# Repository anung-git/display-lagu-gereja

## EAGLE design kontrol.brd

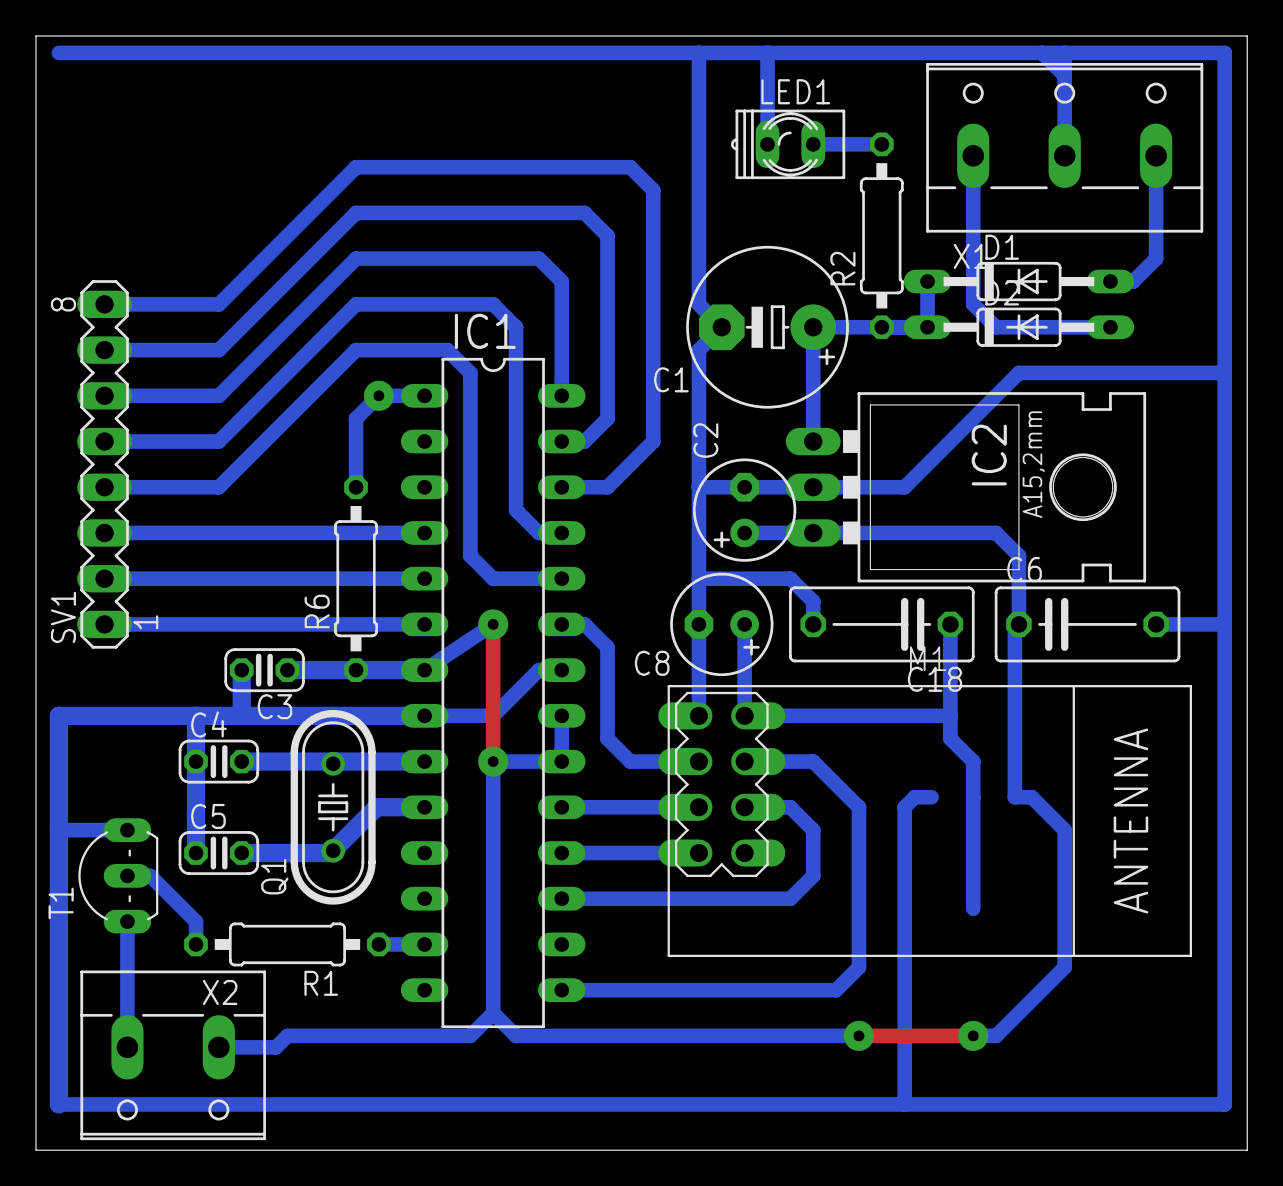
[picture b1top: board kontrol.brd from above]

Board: 2 copper layers, 67.3 x 61.9 mm, 23 parts (1 on the bottom side), 26 nets.

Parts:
C1: E5-8,5
C2, C8: E2,5-6
C3: 100n; C025-024X044
C4, C5: 22p; C025-024X044
C6, C18: C075-042X103
D1, D2: 1N4446; DO35-10
IC1: ATMega88*; DIL28-3
IC2: 78XXL
IC4: MC33269ST-5.0T3; SOT223
LED1: Q62902-B152
M1: WIRELESS-NRF24L01
Q1: 12MHz; HC49/S
R1, R2, R6: 10k; 0207/10
SV1: MA08-1
T1: TO92-CBE
X1: W237-3E
X2: W237-132

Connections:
+5V: C2.+, C3.1, C6.1, IC1.7, IC1.20, IC1.21, IC2.OUT, IC4.3, R6.1, X2.1
+5V1: C8.+, C18.1, IC4.2, IC4.4, M1.2
GND: C1.-, C2.-, C3.2, C4.1, C5.1, C6.2, C8.-, C18.2, IC1.8, IC1.22, IC2.GND, IC4.1, LED1.K, M1.1, T1.E, X1.2
unnamed: IC1.1, R6.2
unnamed: IC1.6, SV1.1
unnamed: IC1.5, SV1.2
unnamed: IC1.4, SV1.3
unnamed: IC1.24, SV1.4
unnamed: IC1.17, M1.6
unnamed: IC1.25, SV1.5
unnamed: IC1.26, SV1.8
unnamed: IC1.18, M1.7
unnamed: IC1.19, M1.5
unnamed: IC1.23, M1.3
unnamed: IC1.15, M1.4
unnamed: IC1.27, SV1.7
unnamed: IC1.28, SV1.6
unnamed: C1.+, D1.C, D2.C, IC2.IN, R2.1
unnamed: D2.A, X1.1
unnamed: D1.A, X1.3
unnamed: T1.C, X2.2
unnamed: IC1.13, R1.1
unnamed: R1.2, T1.B
unnamed: LED1.A, R2.2
unnamed: C4.2, IC1.9, Q1.2
unnamed: C5.2, IC1.10, Q1.1

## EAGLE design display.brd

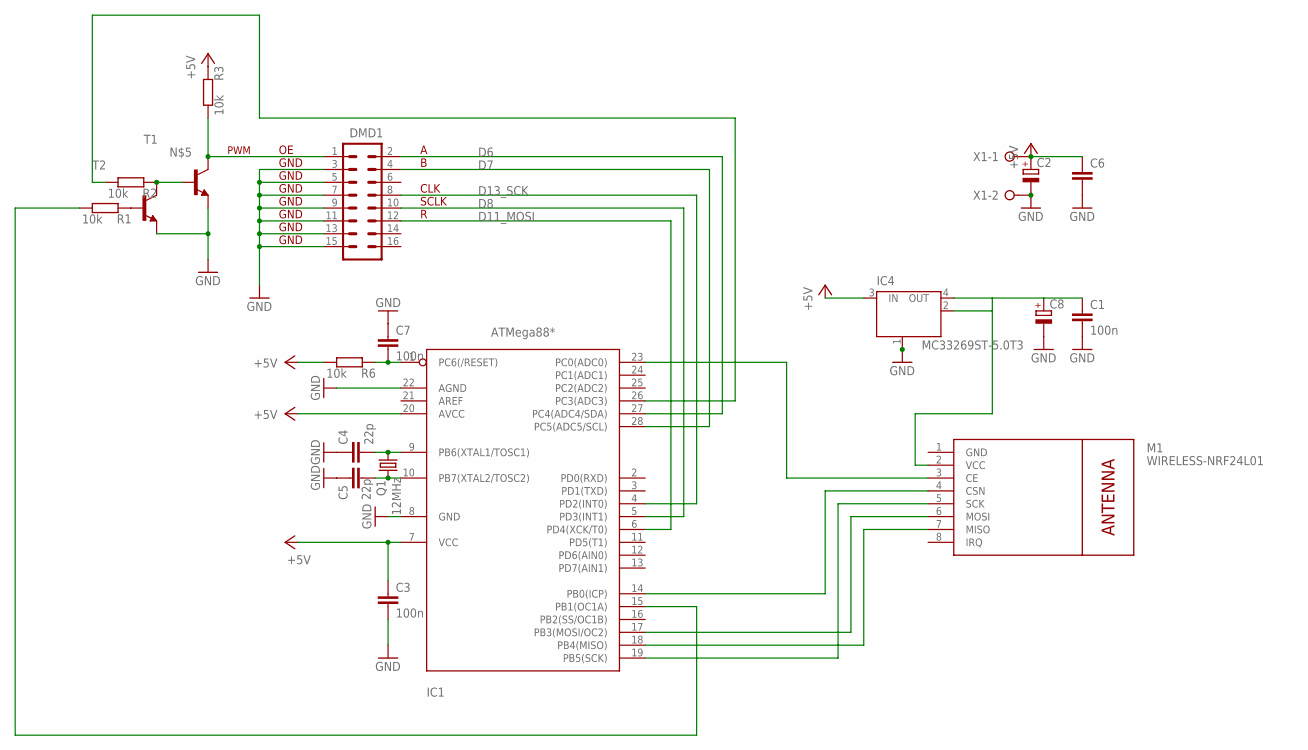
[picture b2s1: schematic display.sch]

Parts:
C1, C3, C7: 100n; C025-024X044
C2, C8: CPOL-EUE2.5-6; E2,5-6
C4, C5: 22p; C025-024X044
C6: C-EU075-042X103; C075-042X103
DMD1: M08X2; 2X8-SMALLERPADS
IC1: ATMega88*; DIL28-3
IC4: MC33269ST-5.0T3; SOT223
M1: WIRELESS-NRF24L01
Q1: 12MHz; HC49/S
R1, R2, R3, R6: 10k; 0207/10
T1, T2: BC548-NPN-TO92-CBE; TO92-CBE
X1: W237-02P; W237-132

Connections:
+5V: C2.+, C3.1, C6.1, IC1.7 (VCC), IC1.20 (AVCC), IC4.3 (IN), R3.2, R6.1, X1.1
+5V1: C1.1, C8.+, IC4.2 (OUT), IC4.4 (OUT), M1.2 (VCC)
D6: DMD1.2, IC1.27 (PC4(ADC4/SDA))
D7: DMD1.4, IC1.28 (PC5(ADC5/SCL))
D8: DMD1.10, IC1.5 (PD3(INT1))
D9: IC1.26 (PC3(ADC3)), R2.1
D11_MOSI: DMD1.12, IC1.6 (PD4(XCK/T0))
D13_SCK: DMD1.8, IC1.4 (PD2(INT0))
GND: C1.2, C2.-, C3.2, C4.1, C5.1, C6.2, C7.1, C8.-, DMD1.3, DMD1.5, DMD1.7, DMD1.9, DMD1.11, DMD1.13, DMD1.15, IC1.8 (GND), IC1.22 (AGND), IC4.1 (GND/ADJ), M1.1 (GND), T1.E, T2.E, X1.2
unnamed: C7.2, IC1.1 (PC6(/RESET)), R6.2
unnamed: R2.2, T1.B, T2.C
unnamed: R1.2, T2.B
unnamed: IC1.15 (PB1(OC1A)), R1.1
unnamed: DMD1.1, R3.1, T1.C
unnamed: IC1.17 (PB3(MOSI/OC2)), M1.6 (MOSI)
unnamed: IC1.18 (PB4(MISO)), M1.7 (MISO)
unnamed: IC1.19 (PB5(SCK)), M1.5 (SCK)
unnamed: IC1.23 (PC0(ADC0)), M1.3 (CE)
unnamed: IC1.14 (PB0(ICP)), M1.4 (CSN)
unnamed: C4.2, IC1.9 (PB6(XTAL1/TOSC1)), Q1.2
unnamed: C5.2, IC1.10 (PB7(XTAL2/TOSC2)), Q1.1

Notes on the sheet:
GND
CLK
SCLK
PWM

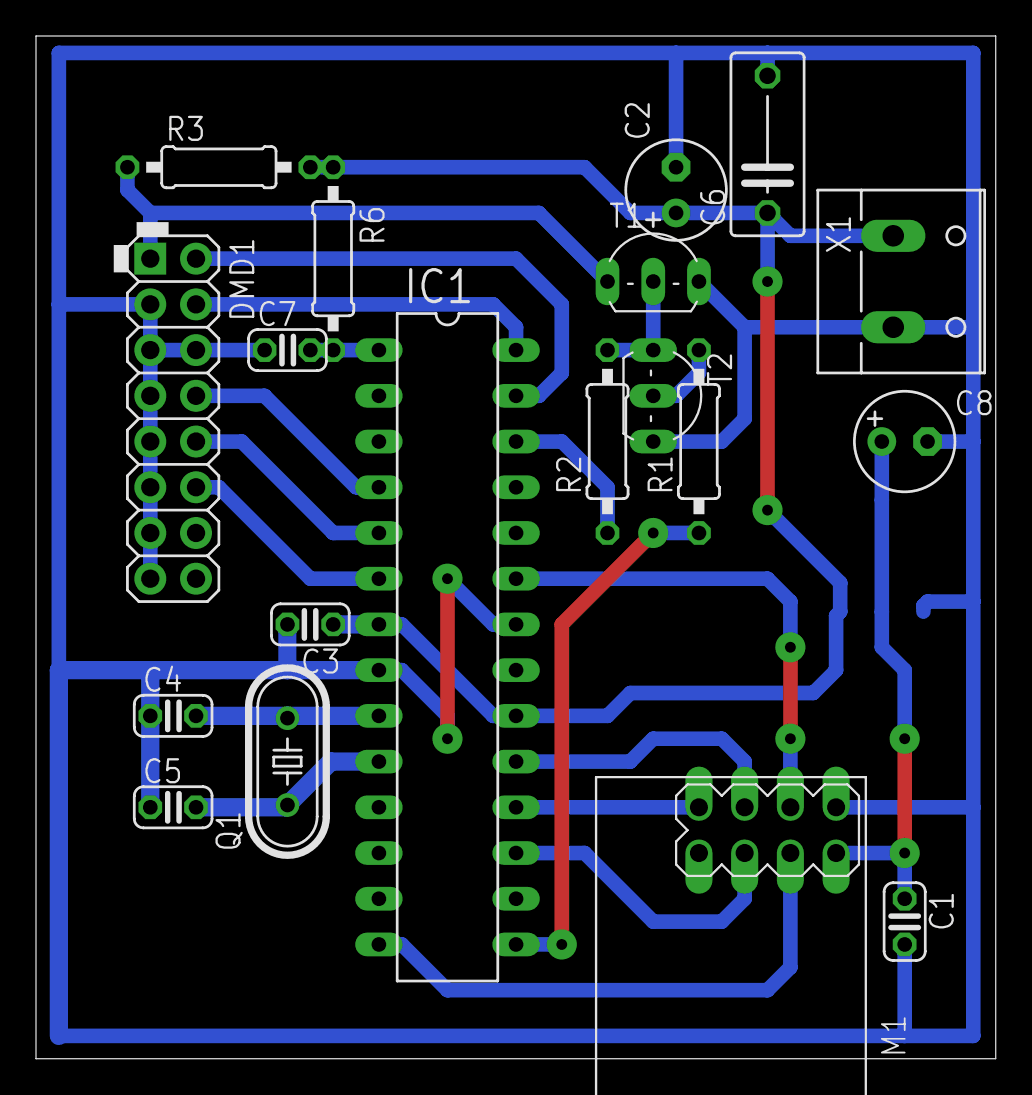
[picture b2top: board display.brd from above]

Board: 2 copper layers, 53.3 x 56.8 mm, 20 parts (1 on the bottom side), 21 nets.

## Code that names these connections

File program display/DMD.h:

/*--------------------------------------------------------------------------------------

 DMD.h   - Function and support library for the Freetronics DMD, a 512 LED matrix display
           panel arranged in a 32 x 16 layout.

 Copyright (C) 2011 Marc Alexander (info <at> freetronics <dot> com)

 Note that the DMD library uses the SPI port for the fastest, low overhead writing to the
 display. Keep an eye on conflicts if there are any other devices running from the same
 SPI port, and that the chip select on those devices is correctly set to be inactive
 when the DMD is being written to.


LED Panel Layout in RAM
                            32 pixels (4 bytes)
        top left  ----------------------------------------
                  |                                      |
         Screen 1 |        512 pixels (64 bytes)         | 16 pixels
                  |                                      |
                  ---------------------------------------- bottom right

 ---
 
 This program is free software: you can redistribute it and/or modify it under the terms
 of the version 3 GNU General Public License as published by the Free Software Foundation.

 This program is distributed in the hope that it will be useful, but WITHOUT ANY WARRANTY;
 without even the implied warranty of MERCHANTABILITY or FITNESS FOR A PARTICULAR PURPOSE.
 See the GNU General Public License for more details.

 You should have received a copy of the GNU General Public License along with this program.
 If not, see <http://www.gnu.org/licenses/>.

--------------------------------------------------------------------------------------*/
#ifndef DMD_H_
#define DMD_H_

//Arduino toolchain header, version dependent
#if defined(ARDUINO) && ARDUINO >= 100
	#include "Arduino.h"
#else
	#include "WProgram.h"
#endif

//SPI library must be included for the SPI scanning/connection method to the DMD
#include "pins_arduino.h"
#include <avr/pgmspace.h>

// ######################################################################################################################
// ######################################################################################################################
#warning CHANGE THESE TO SEMI-ADJUSTABLE PIN DEFS!
//Arduino pins used for the display connection
#define PIN_DMD_nOE       9    // D9 active low Output Enable, setting this low lights all the LEDs in the selected rows. Can pwm it at very high frequency for brightness control.
#define PIN_DMD_A         6    // D6
#define PIN_DMD_B         7    // D7
#define PIN_DMD_CLK       13   // D13_SCK  is SPI Clock if SPI is used
#define PIN_DMD_SCLK      8    // D8
#define PIN_DMD_R_DATA    11   // D11_MOSI is SPI Master Out if SPI is used
//Define this chip select pin that the Ethernet W5100 IC or other SPI device uses
//if it is in use during a DMD scan request then scanDisplayBySPI() will exit without conflict! (and skip that scan)
#define PIN_OTHER_SPI_nCS 10
// ######################################################################################################################
// ######################################################################################################################

 /*   PORTB |= _BV(PB0);  //1
     PORTB &= ~_BV(PB0);  //0
     PORTC &= ~_BV(PC3); PORTC &= ~_BV(PC2);
     
     a=c4
     b=c5
     C3
     D2
     D3
     D4
     DDRC |= _BV(PC3);
     DDRC |= _BV(PC4);
     DDRC |= _BV(PC5);
     DDRD |= _BV(PD2);
     DDRD |= _BV(PD3);
     DDRD |= _BV(PD4);
 */

//DMD I/O pin macros
#define LIGHT_DMD_ROW_01_05_09_13()      { PORTC &= ~_BV(PC5); PORTC &= ~_BV(PC4); }// { digitalWrite( PIN_DMD_B,  LOW ); digitalWrite( PIN_DMD_A,  LOW ); }
#define LIGHT_DMD_ROW_02_06_10_14()      { PORTC &= ~_BV(PC5); PORTC |= _BV(PC4); } // { digitalWrite( PIN_DMD_B,  LOW ); digitalWrite( PIN_DMD_A, HIGH ); }
#define LIGHT_DMD_ROW_03_07_11_15()      { PORTC |= _BV(PC5); PORTC &= ~_BV(PC4); } // { digitalWrite( PIN_DMD_B, HIGH ); digitalWrite( PIN_DMD_A,  LOW ); }
#define LIGHT_DMD_ROW_04_08_12_16()      { PORTC |= _BV(PC5); PORTC |= _BV(PC4); }// { digitalWrite( PIN_DMD_B, HIGH ); digitalWrite( PIN_DMD_A, HIGH ); }
#define LATCH_DMD_SHIFT_REG_TO_OUTPUT()  { PORTD |= _BV(PD3); PORTD &= ~_BV(PD3); } //  { digitalWrite( PIN_DMD_SCLK, HIGH ); digitalWrite( PIN_DMD_SCLK,  LOW ); }
#define OE_DMD_ROWS_OFF()                { PORTC |= _BV(PC3);}// { digitalWrite( PIN_DMD_nOE, LOW  ); }
#define OE_DMD_ROWS_ON()                 { PORTC &= ~_BV(PC3);}// { digitalWrite( PIN_DMD_nOE, HIGH ); }

//Pixel/graphics writing modes (bGraphicsMode)
#define GRAPHICS_NORMAL    0
#define GRAPHICS_INVERSE   1
#define GRAPHICS_TOGGLE    2
#define GRAPHICS_OR        3
#define GRAPHICS_NOR       4

//drawTestPattern Patterns
#define PATTERN_ALT_0     0
#define PATTERN_ALT_1     1
#define PATTERN_STRIPE_0  2
#define PATTERN_STRIPE_1  3

//display screen (and subscreen) sizing
#define DMD_PIXELS_ACROSS         32      //pixels across x axis (base 2 size expected)
#define DMD_PIXELS_DOWN           16      //pixels down y axis
#define DMD_BITSPERPIXEL           1      //1 bit per pixel, use more bits to allow for pwm screen brightness control
#define DMD_RAM_SIZE_BYTES        ((DMD_PIXELS_ACROSS*DMD_BITSPERPIXEL/8)*DMD_PIXELS_DOWN)
                                  // (32x * 1 / 8) = 4 bytes, * 16y = 64 bytes per screen here.
//lookup table for DMD::writePixel to make the pixel indexing routine faster
static byte bPixelLookupTable[8] =
{
   0x80,   //0, bit 7
   0x40,   //1, bit 6
   0x20,   //2. bit 5
   0x10,   //3, bit 4
   0x08,   //4, bit 3
   0x04,   //5, bit 2
   0x02,   //6, bit 1
   0x01    //7, bit 0
};

// Font Indices
#define FONT_LENGTH             0
#define FONT_FIXED_WIDTH        2
#define FONT_HEIGHT             3
#define FONT_FIRST_CHAR         4
#define FONT_CHAR_COUNT         5
#define FONT_WIDTH_TABLE        6

typedef uint8_t (*FontCallback)(const uint8_t*);


//The main class of DMD library functions
class DMD
{
  public:
    //Instantiate the DMD
    DMD(byte panelsWide, byte panelsHigh);
	//virtual ~DMD();

  //Set or clear a pixel at the x and y location (0,0 is the top left corner)
  void writePixel( unsigned int bX, unsigned int bY, byte bGraphicsMode, byte bPixel );

  //Draw a string
  void drawString( int bX, int bY, const char* bChars, byte length, byte bGraphicsMode);

  //Select a text font
  void selectFont(const uint8_t* font);

  //Draw a single character
  int drawChar(const int bX, const int bY, const unsigned char letter, byte bGraphicsMode);

  //Find the width of a character
  int charWidth(const unsigned char letter);

  void shiftOutFast( byte _val);

  //Draw a scrolling string
  void drawMarquee( const char* bChars, byte length, int left, int top);

  //Move the maquee accross by amount
  boolean stepMarquee( int amountX, int amountY);

  //Clear the screen in DMD RAM
  void clearScreen( byte bNormal );

  //Draw or clear a line from x1,y1 to x2,y2
  void drawLine( int x1, int y1, int x2, int y2, byte bGraphicsMode );

  //Draw or clear a circle of radius r at x,y centre
  void drawCircle( int xCenter, int yCenter, int radius, byte bGraphicsMode );

  //Draw or clear a box(rectangle) with a single pixel border
  void drawBox( int x1, int y1, int x2, int y2, byte bGraphicsMode );

  //Draw or clear a filled box(rectangle) with a single pixel border
  void drawFilledBox( int x1, int y1, int x2, int y2, byte bGraphicsMode );

  //Draw the selected test pattern
  void drawTestPattern( byte bPattern );

  //Scan the dot matrix LED panel display, from the RAM mirror out to the display hardware.
  //Call 4 times to scan the whole display which is made up of 4 interleaved rows within the 16 total rows.
  //Insert the calls to this function into the main loop for the highest call rate, or from a timer interrupt
  void scanDisplayBySPI();


  private:
    void drawCircleSub( int cx, int cy, int x, int y, byte bGraphicsMode );

    //Mirror of DMD pixels in RAM, ready to be clocked out by the main loop or high speed timer calls
    byte *bDMDScreenRAM;

    //Marquee values
    char marqueeText[256];
    byte marqueeLength;
    int marqueeWidth;
    int marqueeHeight;
    int marqueeOffsetX;
    int marqueeOffsetY;

    //Pointer to current font
    const uint8_t* Font;

    //Display information
    byte DisplaysWide;
    byte DisplaysHigh;
    byte DisplaysTotal;
    int row1, row2, row3;

    //scanning pointer into bDMDScreenRAM, setup init @ 48 for the first valid scan
    volatile byte bDMDByte;

};

#endif /* DMD_H_ */

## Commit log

2019-04-14 file keterangan
2019-04-14 skema kontrol
2019-04-14 layout display
2019-04-14 skema display
2019-04-14 layout remot
2019-04-14 skema remot
2019-04-14 progam display
2019-04-14 program display arduino
2019-04-14 lib font
2019-04-14 lib dmd cpp
2019-04-14 lib dmd header
2019-04-14 lib nrf header
2019-04-14 lib rf24 cpp
2019-04-14 lib rf24 header
2019-04-14 lib r24 config
2019-04-14 program remot
2019-04-14 program arduino
2019-04-14 lib key cpp
2019-04-14 Keypad cpp
2019-04-14 Keypad h
2019-04-14 RF24 cpp
2019-04-14 RF24 h
2019-04-14 RF24_config

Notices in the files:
parts and their libraries:
diy-modules: Released under the Creative Commons Attribution 4.0 International License: http://creativecommons.org/licenses/by/4.0
